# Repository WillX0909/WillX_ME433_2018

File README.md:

# WillX_ME433_2018

Advanced Embedded System Programming.  

Prof: Nick Marchuk. 

Northwestern University

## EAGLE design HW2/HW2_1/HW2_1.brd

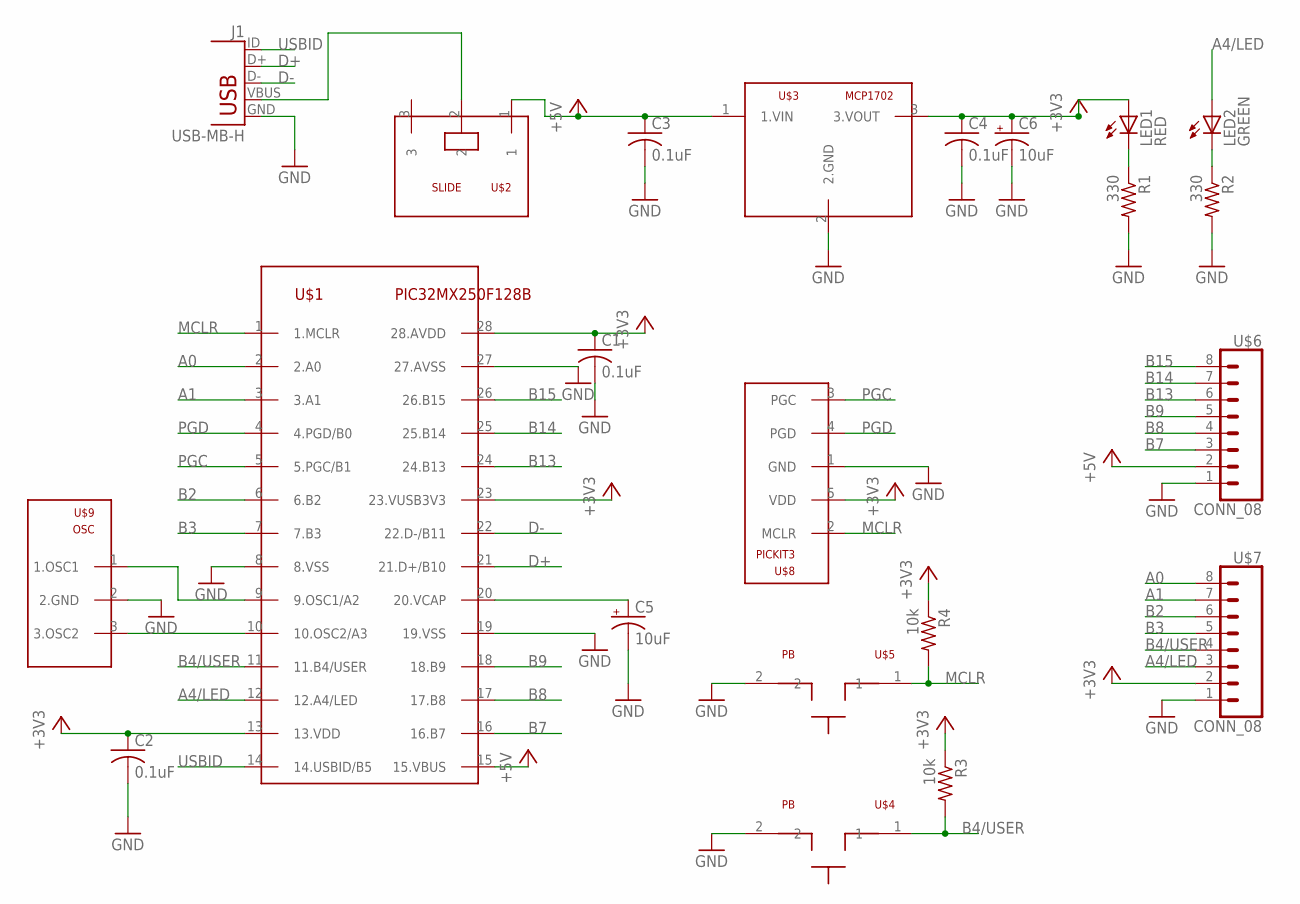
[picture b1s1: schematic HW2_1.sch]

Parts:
C1, C2, C3, C4: 0.1uF; C025-025X050
C5, C6: 10uF; B45181B
J1: USB-MB-H
LED1: RED; LED3MM
LED2: GREEN; LED3MM
R1, R2: 330; 0207/7
R3, R4: 10k; 0207/7
U$1: PIC32MX250F128B; DIL28-3
U$2: SLIDE
U$3: MCP1702; TO92
U$4, U$5: PB
U$6, U$7: CONN_08; 1X08
U$8: PICKIT3; 1X05
U$9: OSC

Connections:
+3V3: C1.1, C2.1, C4.1, C6.+, LED1.A, R3.1, R4.1, U$1.13 (13.VDD), U$1.23 (23.VUSB3V3), U$1.28 (28.AVDD), U$3.3 (3.VOUT), U$7.2, U$8.5 (VDD)
+5V: C3.1, U$1.15 (15.VBUS), U$2.1, U$3.1 (1.VIN), U$6.2
A0: U$1.2 (2.A0), U$7.8
A1: U$1.3 (3.A1), U$7.7
A4/LED: LED2.A, U$1.12 (12.A4/LED), U$7.3
B2: U$1.6 (6.B2), U$7.6
B3: U$1.7 (7.B3), U$7.5
B4/USER: R3.2, U$1.11 (11.B4/USER), U$4.1, U$7.4
B7: U$1.16 (16.B7), U$6.3
B8: U$1.17 (17.B8), U$6.4
B9: U$1.18 (18.B9), U$6.5
B13: U$1.24 (24.B13), U$6.6
B14: U$1.25 (25.B14), U$6.7
B15: U$1.26 (26.B15), U$6.8
D+: J1.D+, U$1.21 (21.D+/B10)
D-: J1.D-, U$1.22 (22.D-/B11)
GND: C1.2, C2.2, C3.2, C4.2, C5.-, C6.-, J1.GND, R1.2, R2.2, U$1.8 (8.VSS), U$1.19 (19.VSS), U$1.27 (27.AVSS), U$3.2 (2.GND), U$4.2, U$5.2, U$6.1, U$7.1, U$8.1 (GND), U$9.2 (2.GND)
MCLR: R4.2, U$1.1 (1.MCLR), U$5.1, U$8.2 (MCLR)
unnamed: J1.VBUS, U$2.2
unnamed: LED1.K (C), R1.1
unnamed: LED2.K (C), R2.1
unnamed: U$1.10 (10.OSC2/A3), U$9.3 (3.OSC2)
unnamed: U$1.9 (9.OSC1/A2), U$9.1 (1.OSC1)
unnamed: C5.+, U$1.20 (20.VCAP)
PGC: U$1.5 (5.PGC/B1), U$8.3 (PGC)
PGD: U$1.4 (4.PGD/B0), U$8.4 (PGD)
USBID: J1.ID, U$1.14 (14.USBID/B5)

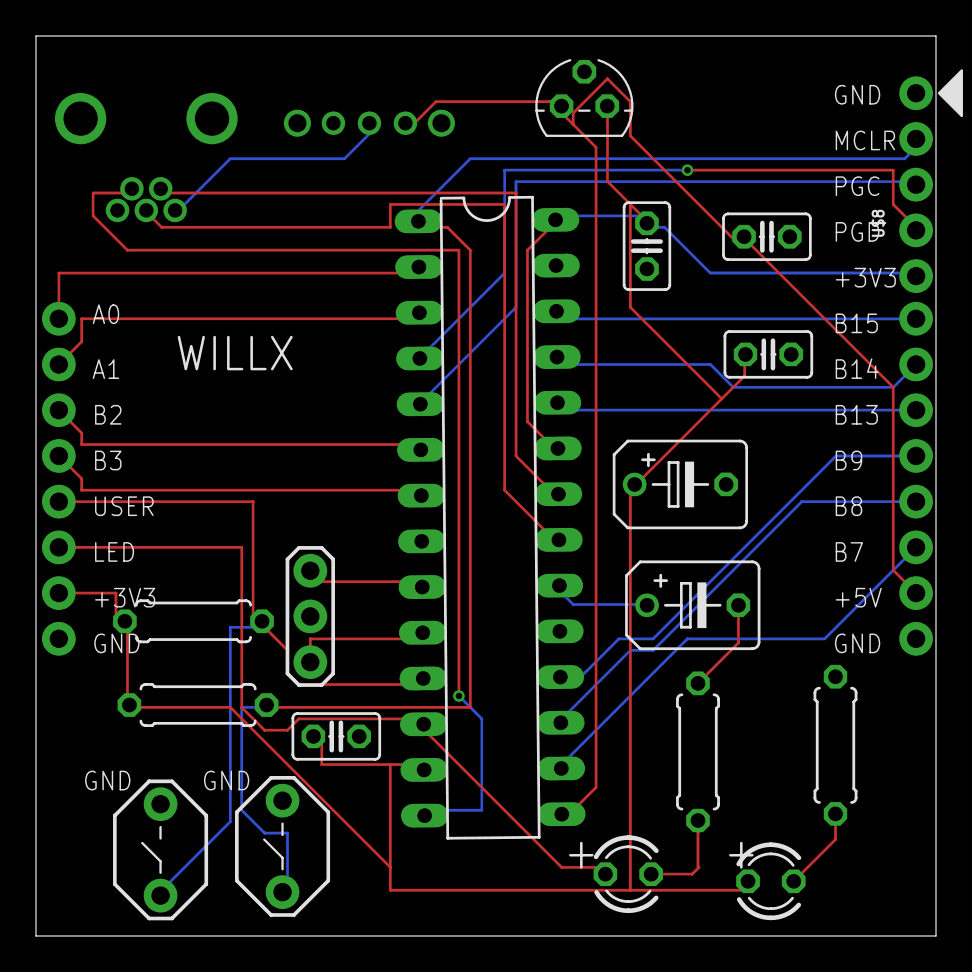
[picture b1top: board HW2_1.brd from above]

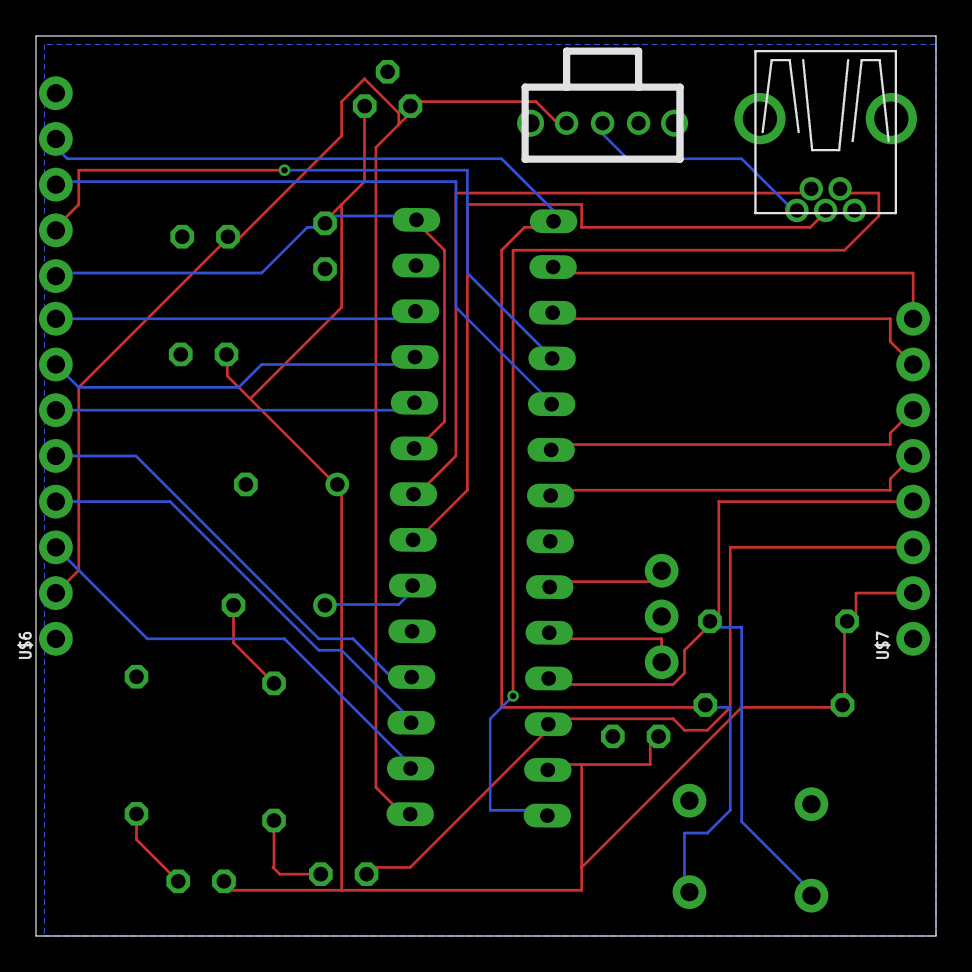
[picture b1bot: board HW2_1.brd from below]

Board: 2 copper layers, 50.0 x 50.0 mm, 22 parts (3 on the bottom side), 27 nets.

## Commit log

2018-04-05 basic programs
    #pragma input
2018-04-07 basic1
2018-04-07 not_full
2018-04-10 hw2_lib
2018-04-11 change of sch and board
2018-04-11 demo1
2018-04-15 add final board and sch
2018-04-18 hw4 base
2018-04-19 Add images
2018-04-21 hw5_demo
2018-04-21 updated main
2018-04-21 update main
2018-04-21 schematic
2018-04-24 hw6 base
2018-04-24 add demo
2018-04-27 hw7 base
2018-04-27 change freq
2018-04-27 HW7final
2018-05-01 hw8 base
2018-05-03 HW9 base
2018-05-09 HW9 FINAL
2018-05-10 HW10 BASE
2018-05-10 HW10 FINAL
2018-05-10 HW11 FINAL
2018-05-10 hw11 demo
2018-05-16 hw12 base
2018-05-20 hw12
2018-05-20 hw12 demo
2018-05-20 hw13
2018-05-20 hw13 demo
2018-05-23 hw14
2018-05-25 hw14_pass
2018-06-08 HW17
2018-06-11 HW16
2018-06-11 HW15
2018-06-12 HW18
2018-06-12 read me
